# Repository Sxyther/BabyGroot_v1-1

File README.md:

# babygroot_v1-1
BabyGroot version 1.1 

---------------------------------------------------------------------------------------------------------------------
Software License: GPL v3

---------------------------------------------------------------------------------------------------------------------
Hardware License: CERN
Hardware released under an CERN Open Hardware Licence v1.2. See the LICENSE_HARDWARE file for more information.

---------------------------------------------------------------------------------------------------------------------
Documentation License: Creative Commons
Esta obra está bajo una Licencia Creative Commons Atribución-CompartirIgual 4.0 Internacional.

MakersGDL is a registered trademark, please do not use if you reproduce to sell PCBs.

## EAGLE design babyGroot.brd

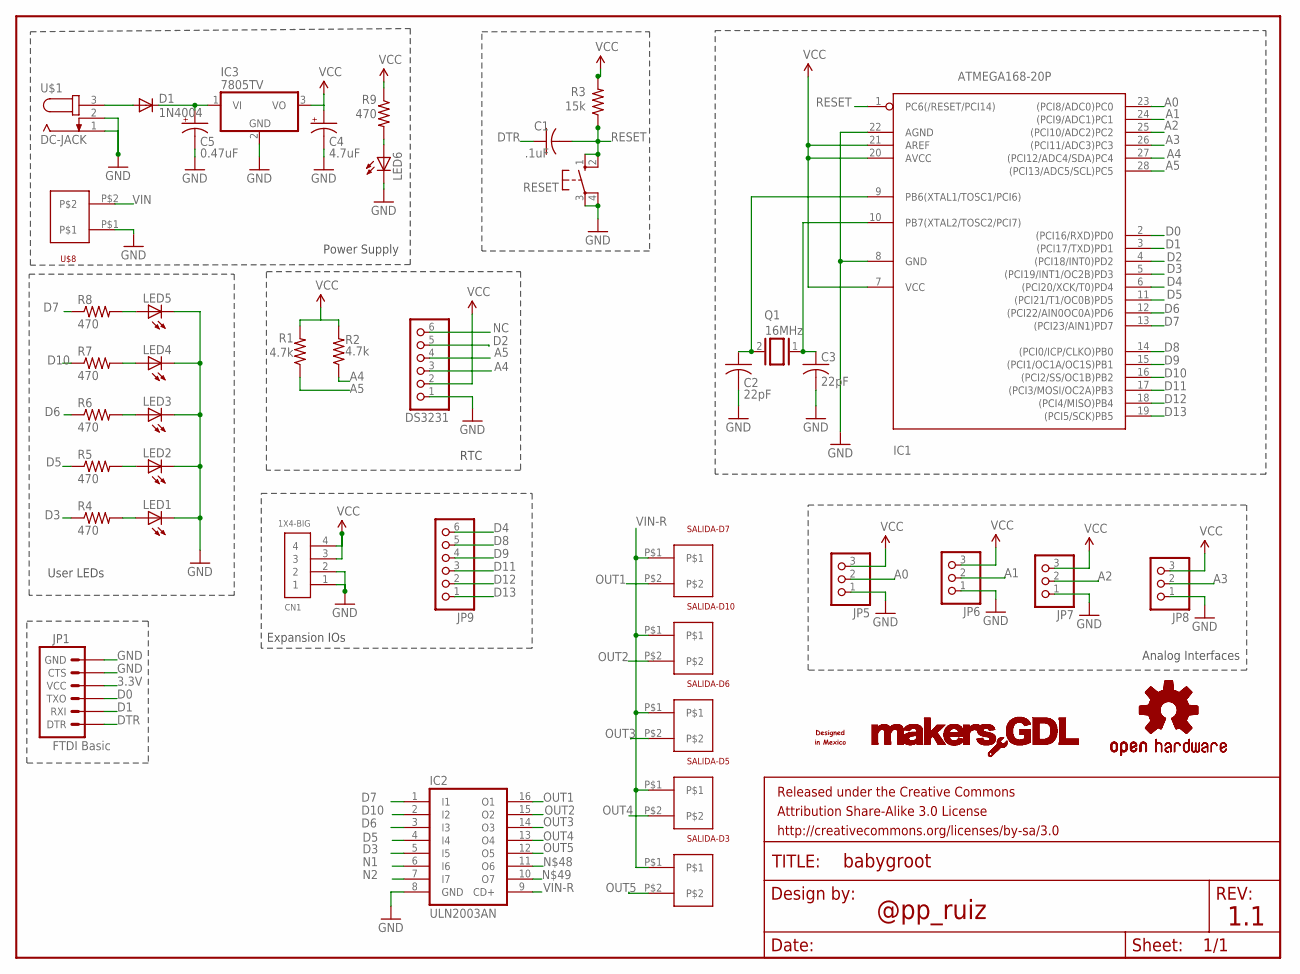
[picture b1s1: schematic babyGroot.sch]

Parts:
C1: .1uF; C025-024X044
C2, C3: 22pF; C025-024X044
C4: 4.7uF; E2,5-6E
C5: 0.47uF; E2,5-6E
CN1: 1X4-BIG; 1X04-BIG
D1: 1N4004; DO41-10
DS3231: PINHD-1X6; 1X06
FRAME1: FRAME-LETTER; CREATIVE_COMMONS
IC1: ATMEGA168-20P; DIL28-3
IC2: ULN2003AN; DIL16
IC3: 7805TV; TO220V
JP1: FTDI Basic; 1X06
JP5, JP6, JP7, JP8: PINHD-1X3; 1X03
JP9: PINHD-1X6; 1X06
LED1, LED2, LED3, LED4, LED5, LED6: LED3MM
Q1: 16MHz; QS
R1, R2: 4.7k; 0204V
R3: 15k; 0204V
R4, R5, R6, R7, R8, R9: 470; 0204V
RESET: 10-XX; B3F-10XX
SALIDA-D3, SALIDA-D5, SALIDA-D6, SALIDA-D7, SALIDA-D10: 2POSHEADER-0.5MM; 2PIN-0.5MM
U$1: DC-JACK; SPC4078
U$2, U$4: MAKERSGDLLOGO-SMALL; MAKERSGGL-SMALL
U$3, U$5: OSHW-LOGOS; OSHW-LOGO-S
U$6: DESIGNEDMEXICO
U$8: 2POSHEADER-0.5MM; 2PIN-0.5MM

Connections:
3.3V: C4.+, CN1.3, CN1.4, DS3231.2, IC1.7 (VCC), IC1.20 (AVCC), IC1.21 (AREF), IC3.3 (VO), JP1.4 (VCC), JP5.3, JP6.3, JP7.3, JP8.3, R1.2, R2.2, R3.2, R9.1
A0: IC1.23 ((PCI8/ADC0)PC0), JP5.2
A1: IC1.24 ((PCI9/ADC1)PC1), JP6.2
A2: IC1.25 ((PCI10/ADC2)PC2), JP7.2
A3: IC1.26 ((PCI11/ADC3)PC3), JP8.2
A4: DS3231.3, IC1.27 ((PCI12/ADC4/SDA)PC4), R2.1
A5: DS3231.4, IC1.28 ((PCI13/ADC5/SCL)PC5), R1.1
D0: IC1.2 ((PCI16/RXD)PD0), JP1.3 (TXO)
D1: IC1.3 ((PCI17/TXD)PD1), JP1.2 (RXI)
D2: DS3231.5, IC1.4 ((PCI18/INT0)PD2)
D3: IC1.5 ((PCI19/INT1/OC2B)PD3), IC2.5 (I5), R4.1
D4: IC1.6 ((PCI20/XCK/T0)PD4), JP9.6
D5: IC1.11 ((PCI21/T1/OC0B)PD5), IC2.4 (I4), R5.1
D6: IC1.12 ((PCI22/AIN0OC0A)PD6), IC2.3 (I3), R6.1
D7: IC1.13 ((PCI23/AIN1)PD7), IC2.1 (I1), R8.1
D8: IC1.14 ((PCI0/ICP/CLKO)PB0), JP9.5
D9: IC1.15 ((PCI1/OC1A/OC1S)PB1), JP9.4
D10: IC1.16 ((PCI2/SS/OC1B)PB2), IC2.2 (I2), R7.1
D11: IC1.17 ((PCI3/MOSI/OC2A)PB3), JP9.3
D12: IC1.18 ((PCI4/MISO)PB4), JP9.2
D13: IC1.19 ((PCI5/SCK)PB5), JP9.1
DTR: C1.1, JP1.1 (DTR)
GND: C2.2, C3.2, C4.-, C5.-, CN1.1, CN1.2, DS3231.1, IC1.8 (GND), IC1.22 (AGND), IC2.8 (GND), IC3.2 (GND), JP1.5 (CTS), JP1.6 (GND), JP5.1, JP6.1, JP7.1, JP8.1, LED1.K (C), LED2.K (C), LED3.K (C), LED4.K (C), LED5.K (C), LED6.K (C), RESET.3, RESET.4 (P1), U$1.1, U$1.2, U$8.P$1
N1: IC2.6 (I6)
N2: IC2.7 (I7)
unnamed: C2.1, IC1.9 (PB6(XTAL1/TOSC1/PCI6)), Q1.2
unnamed: C3.1, IC1.10 (PB7(XTAL2/TOSC2/PCI7)), Q1.1
unnamed: LED6.A, R9.2
unnamed: LED5.A, R8.2
unnamed: LED4.A, R7.2
unnamed: LED3.A, R6.2
unnamed: LED2.A, R5.2
unnamed: LED1.A, R4.2
NC: DS3231.6
OUT1: IC2.16 (O1), SALIDA-D7.P$2
OUT2: IC2.15 (O2), SALIDA-D10.P$2
OUT3: IC2.14 (O3), SALIDA-D6.P$2
OUT4: IC2.13 (O4), SALIDA-D5.P$2
OUT5: IC2.12 (O5), SALIDA-D3.P$2
RESET: C1.2, IC1.1 (PC6(/RESET/PCI14)), R3.1, RESET.1 (S), RESET.2 (S1)
VIN: D1.A, U$1.3, U$8.P$2
VIN-R: C5.+, D1.C, IC2.9 (CD+), IC3.1 (VI), SALIDA-D3.P$1, SALIDA-D5.P$1, SALIDA-D6.P$1, SALIDA-D7.P$1, SALIDA-D10.P$1

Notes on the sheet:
User LEDs
@pp_ruiz
1.1
Power Supply
RTC
Analog Interfaces
Expansion IOs

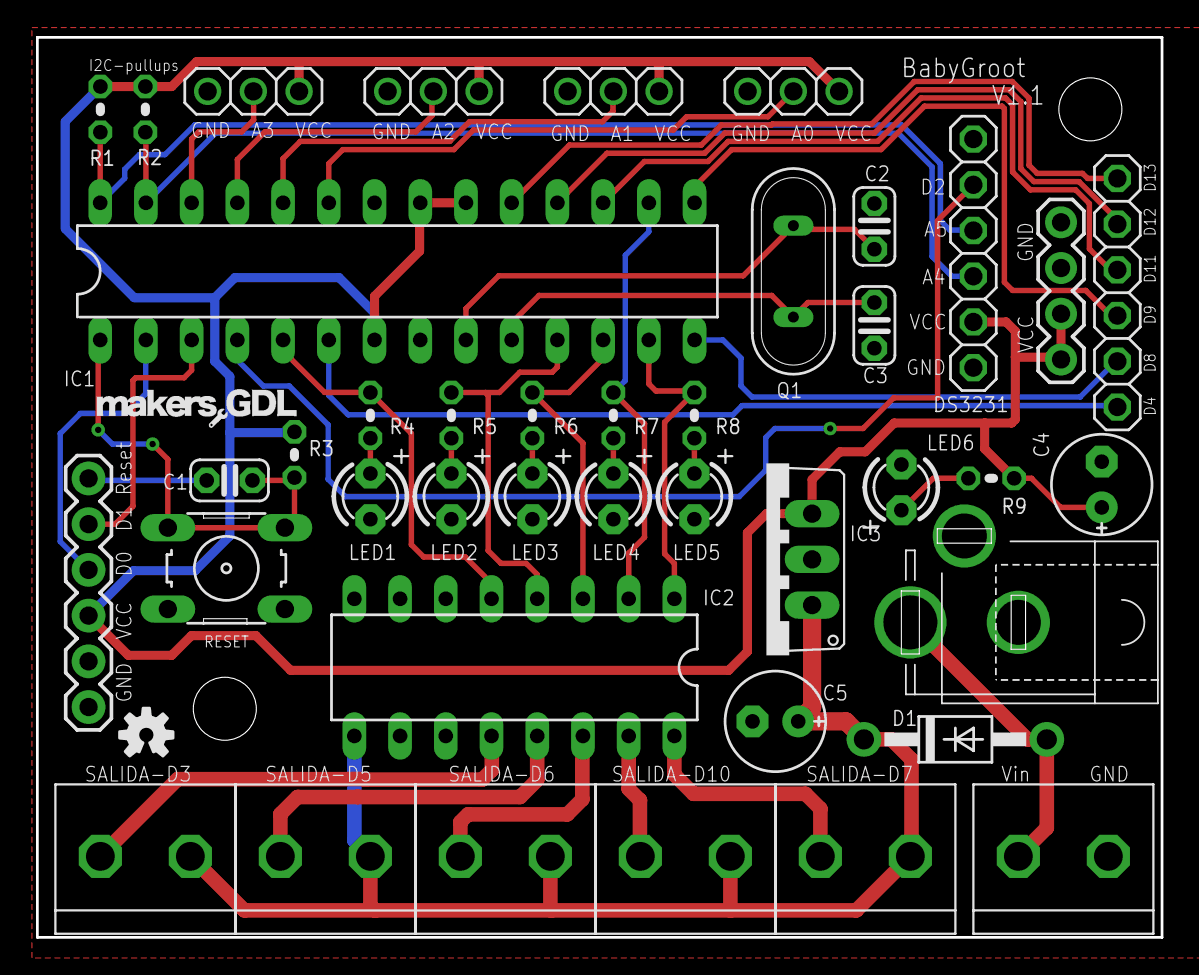
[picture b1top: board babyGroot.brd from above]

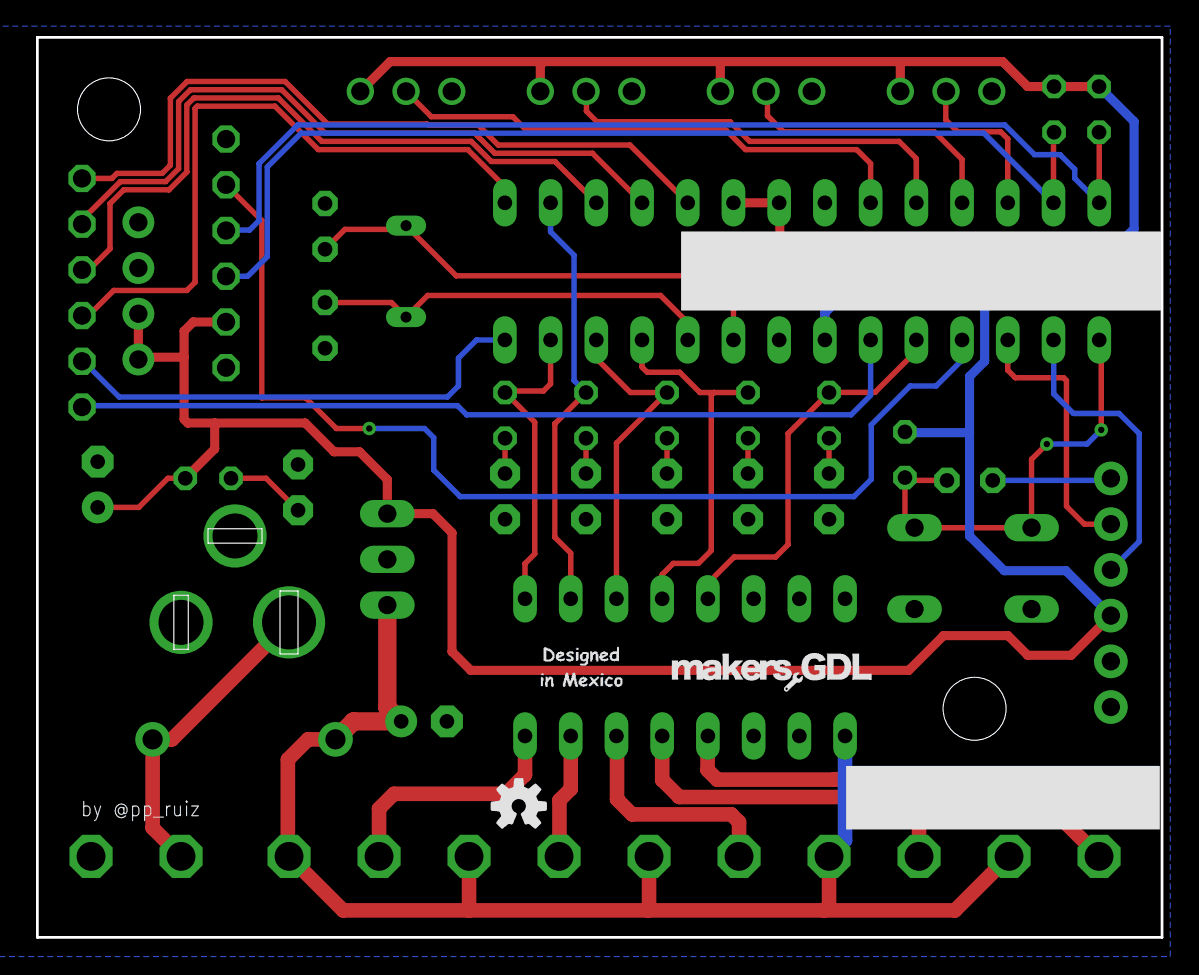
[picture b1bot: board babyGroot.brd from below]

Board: 2 copper layers, 62.5 x 50.0 mm, 47 parts (3 on the bottom side), 39 nets.

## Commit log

2018-09-08 BabyGroot v1.1 Schematic
2018-09-08 Design Files
2018-09-08 Manual de BabyGroot

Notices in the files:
parts and their libraries:
SparkFun-Aesthetics: Licensing: CC v3.0 Share-Alike You are welcome to use this library for commercial purposes.
SparkFun-Aesthetics: Released under the Creative Commons Attribution Share-Alike 3.0 License
SparkFun-Aesthetics: http://creativecommons.org/licenses/by-sa/3.0
